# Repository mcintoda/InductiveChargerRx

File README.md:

# brim: bath level monitor

A sealed, Qi-charged sensor that suction-mounts in the bathtub. It sends a
notification to your iPhone (over Wi-Fi, no pairing) before the bath
overflows, and reports the water temperature.

- **Level:** a 6-pad capacitive ladder that senses through the enclosure wall (non-contact)
- **Temperature:** TMP117, ±0.1 °C
- **Radio:** ESP32-S3 Wi-Fi → free ntfy push notifications (iOS app)
- **Power:** 320 mAh protected LiPo (25.5 × 36 × 4.3 mm), BQ51050B Qi receiver/charger at 143 mA, ~6 months per charge (estimate). Charges lying flat on any Qi pad, like a phone
- **Build:** JLCPCB 4-layer PCB + SMT assembly, JLC3DP enclosure

> Also in this repo: **[`squeeze/`](squeeze/README.md)**, a pair of hand-held pebbles that pass squeezes back and forth (separate project, reuses brim's Qi charger block).

- [`docs/design.md`](docs/design.md): requirements, architecture, power budget, mechanics, firmware behaviour
- [`docs/placement-and-electrodes.md`](docs/placement-and-electrodes.md): board placement study and electrode design (with field simulation)
- [`docs/sensing-options.md`](docs/sensing-options.md): touch vs FDC1004 level sensing: board variants, compare mode, bench protocol, decision rules
- [`docs/sensing-infographic.html`](docs/sensing-infographic.html): interactive explainer of how the level and temperature sensing work electrically
- [`docs/branding.md`](docs/branding.md): name, mark, palette, and the debossed design features on the enclosure
- [`docs/pcb-routing.md`](docs/pcb-routing.md): routing pipeline and JLC order settings
- [`docs/bring-up.md`](docs/bring-up.md): bench test plan for the first boards
- [`firmware/`](firmware/): ESP-IDF firmware (ESP32-S3) with host unit tests
- **Product requirements (system, hardware, software):** [`docs/requirements.md`](docs/requirements.md)
- **Product website (marketing page):** [`docs/site/index.html`](docs/site/index.html)
- **Security review (Wi-Fi, web, OTA):** [`docs/security.md`](docs/security.md); firmware SBOM and CVE check: [`docs/sbom/`](docs/sbom/README.md)
- **Quick start guide for users:** [`docs/quick-start.html`](docs/quick-start.html) (setup, mounting, alerts, charging, light legend)
- [`docs/enclosure.md`](docs/enclosure.md): watertight enclosure (O-ring, no epoxy) with CAD in [`hardware/mech/`](hardware/mech/)
- **Parts JLC does not supply:** [`docs/bom-hand-parts.md`](docs/bom-hand-parts.md) (one BOM, all suppliers; CSV: [`hardware/bom_hand_parts.csv`](hardware/bom_hand_parts.csv))
- **Schematic without KiCad:** [`docs/schematic.pdf`](docs/schematic.pdf) (zoomable, searchable) or [`docs/img/schematic.svg`](docs/img/schematic.svg) / [`.png`](docs/img/schematic.png) (shows in the browser)
- [`hardware/kicad/`](hardware/kicad/): KiCad 7 project (schematic rev C, routed 4-layer PCB)
- [`hardware/bom_jlc.csv`](hardware/bom_jlc.csv): JLCPCB assembly BOM (generated; LCSC numbers still to be filled)
- [`hardware/tools/gen_schematic.py`](hardware/tools/gen_schematic.py): regenerates the schematic and BOM
- [`hardware/tools/gen_pcb.py`](hardware/tools/gen_pcb.py) / [`electrode_sim.py`](hardware/tools/electrode_sim.py): placement-study PCB and electrode simulation
- [`hardware/tools/verify_netlist.py`](hardware/tools/verify_netlist.py): checks that the drawn wiring matches the intended netlist

```
python3 hardware/tools/gen_schematic.py    # needs KiCad 7+ symbol libraries; also refreshes docs/schematic.pdf/.svg/.png
python3 hardware/tools/verify_netlist.py   # needs kicad-cli
```

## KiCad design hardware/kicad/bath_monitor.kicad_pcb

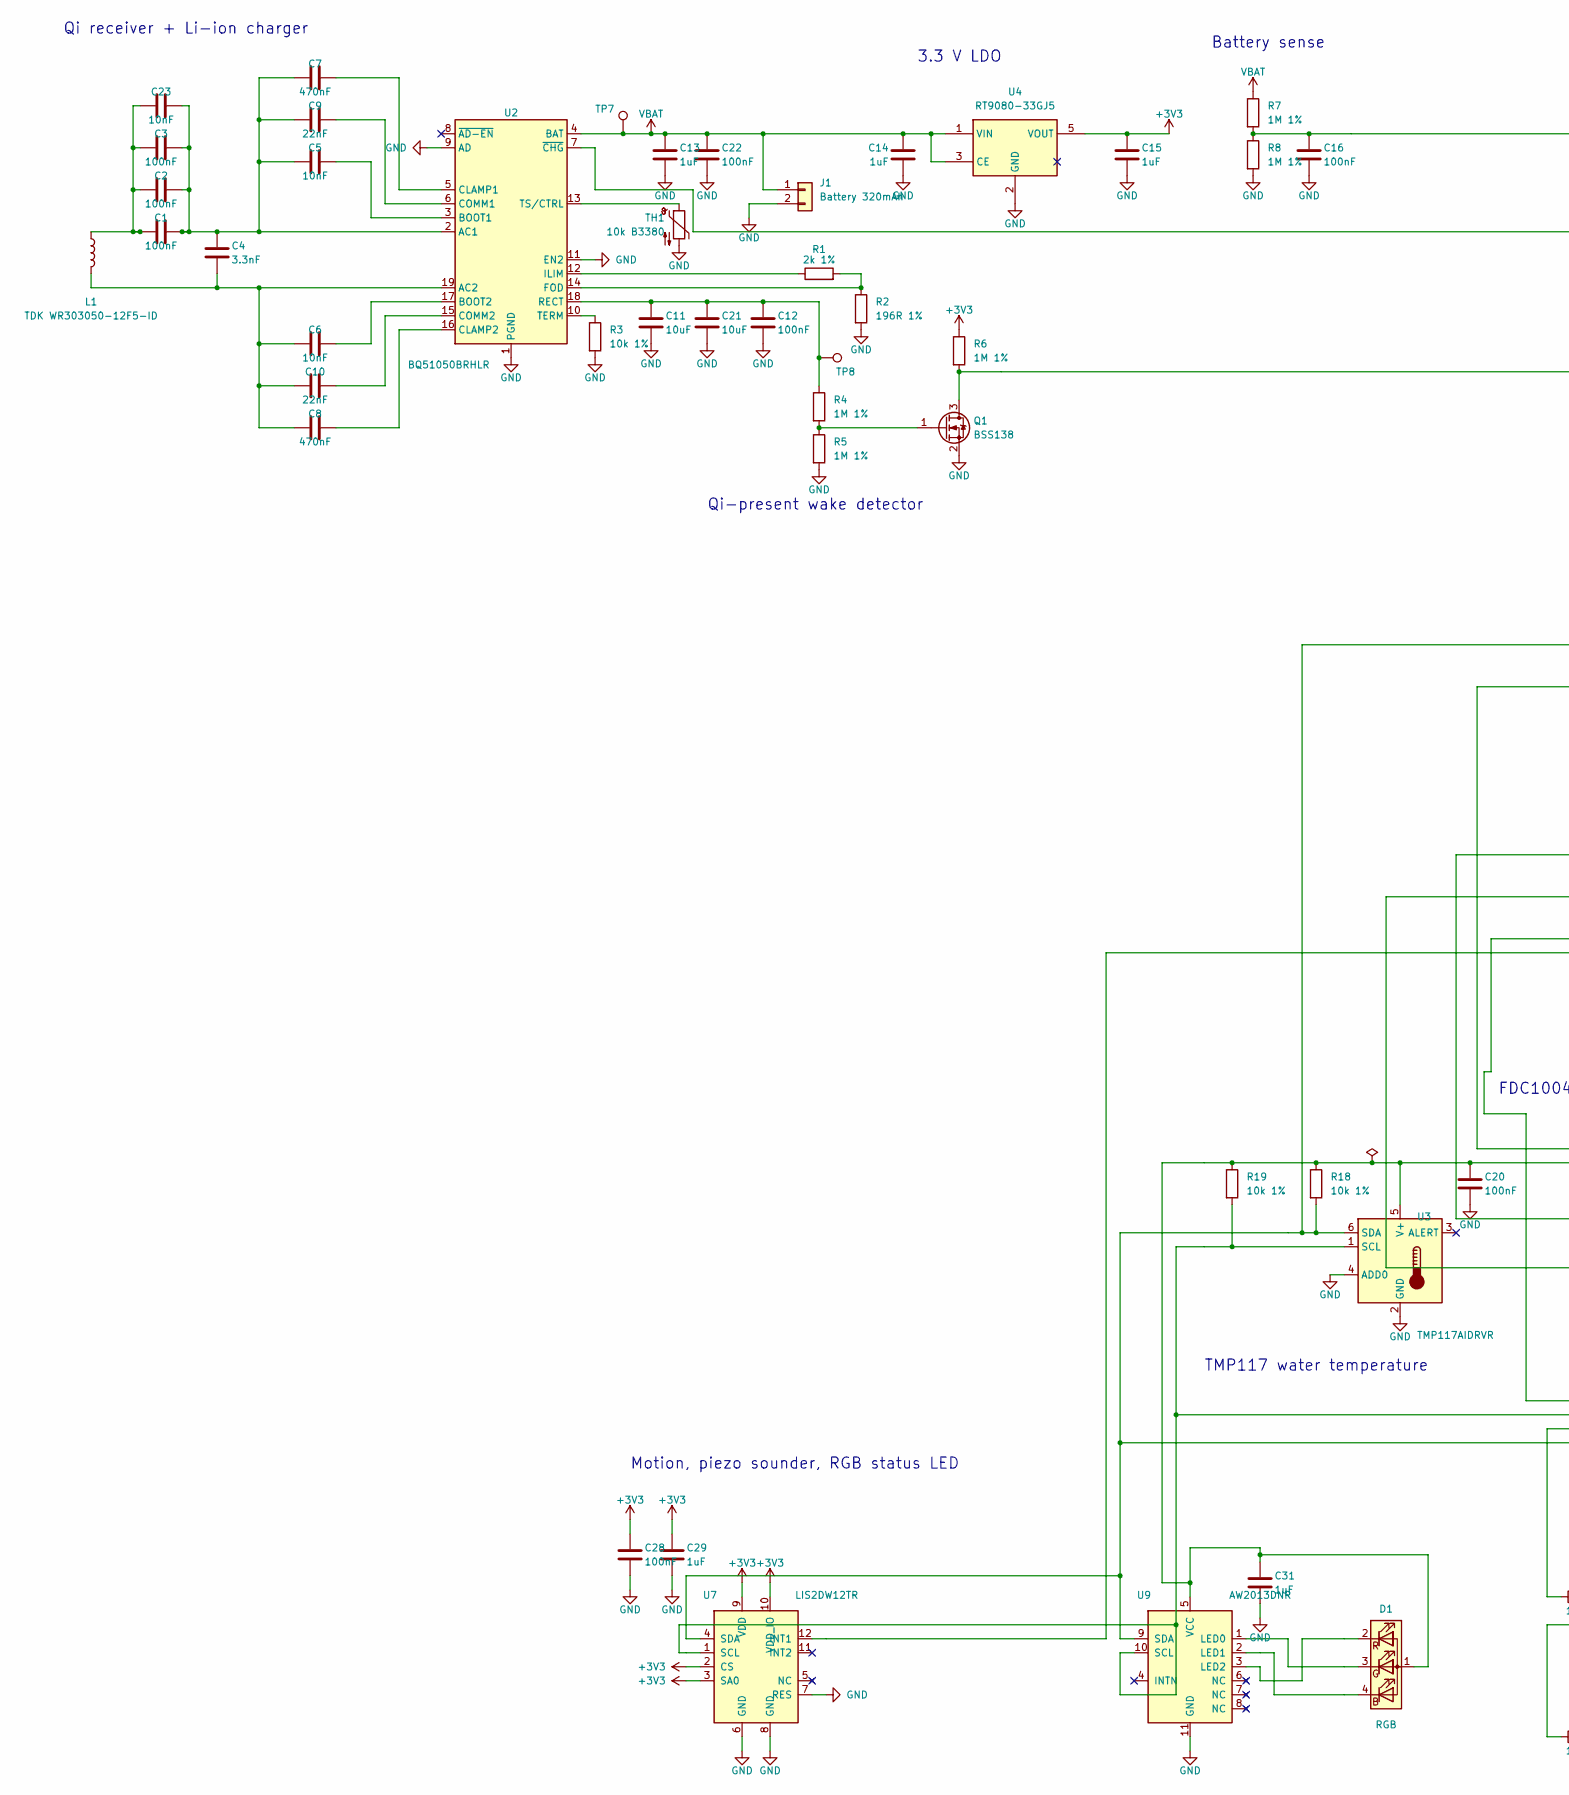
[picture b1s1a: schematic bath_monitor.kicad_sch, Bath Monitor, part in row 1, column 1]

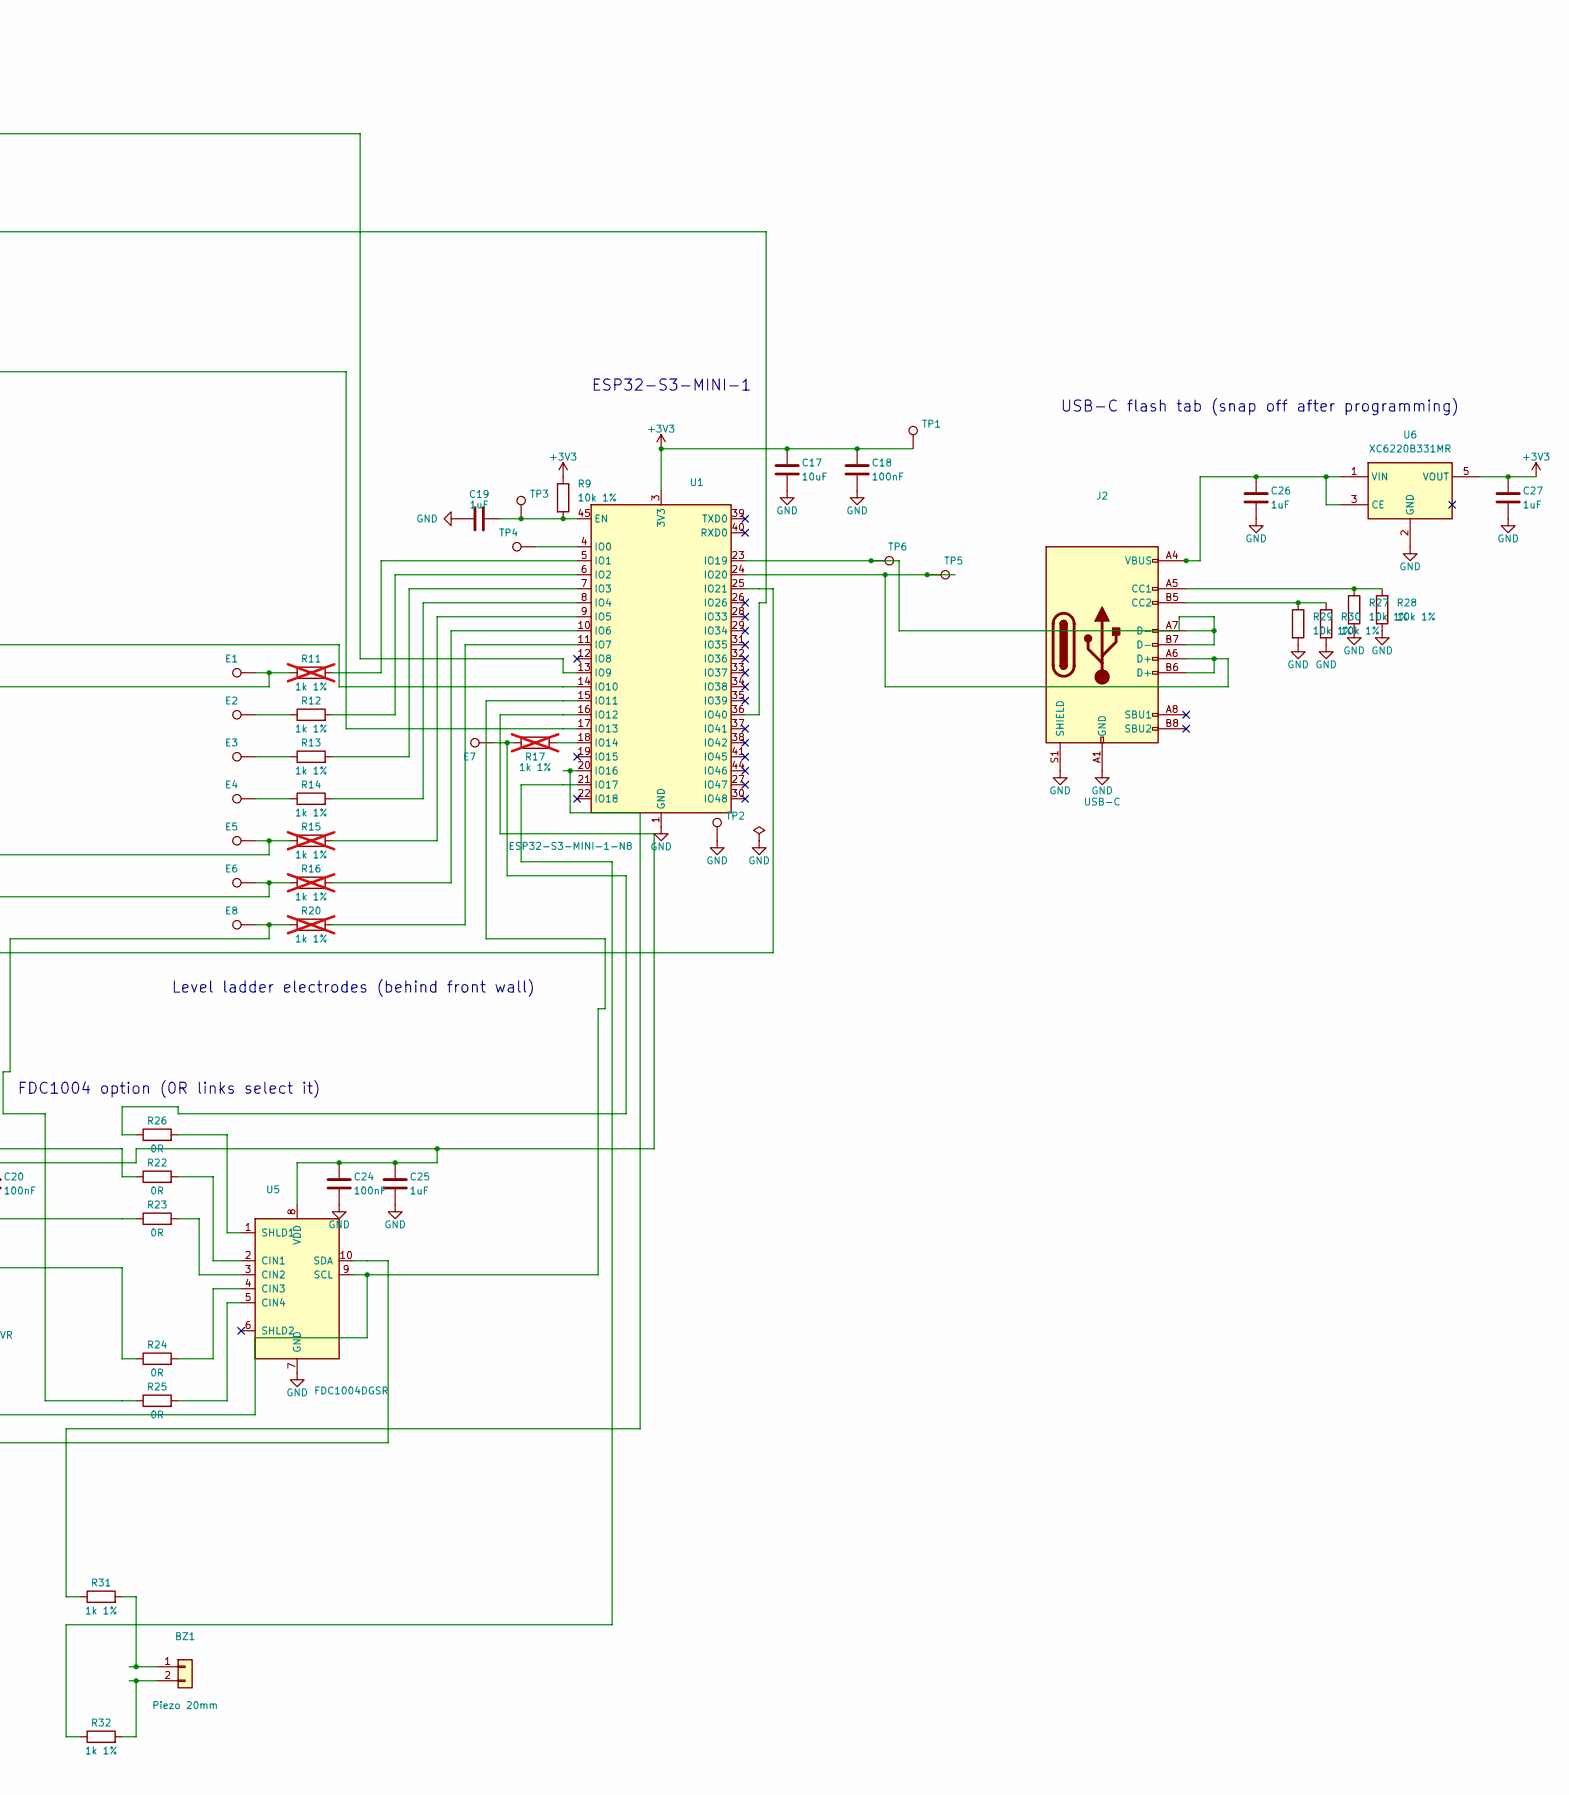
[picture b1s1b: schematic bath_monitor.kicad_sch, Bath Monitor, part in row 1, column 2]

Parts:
BZ1: Piezo 20mm; SolderWirePad_1x02_SMD_1x1.6mm_P2mm
C1, C2, C3, C12, C16, C18, C20, C22, C24, C28: 100nF; C_0603_1608Metric; Rating 50V X7R
C4: 3.3nF; C_0603_1608Metric; Rating 50V C0G
C5, C6, C23: 10nF; C_0402_1005Metric; Rating 50V X7R
C7, C8: 470nF; C_0603_1608Metric; Rating 25V X7R
C9, C10: 22nF; C_0402_1005Metric; Rating 50V X7R
C11, C17, C21: 10uF; C_0805_2012Metric; Rating 25V X5R
C13, C14, C15, C19, C25, C26, C27, C29, C31: 1uF; C_0402_1005Metric; Rating 25V X5R
D1: RGB; LED_RGB_1615_XINGLIGHT; MPN XL-1615RGBC-RF
E1: PAD1; TouchPad_30x9mm
E2: PAD2; TouchPad_30x9mm
E3: PAD3; TouchPad_30x9mm
E4: PAD4; TouchPad_30x9mm
E5: PAD5; TouchPad_30x9mm
E6: PAD6; TouchPad_30x9mm
E7: SHIELD; ShieldTap
E8: REF; RefPad_30x6mm
J1: Battery 320mAh; SolderWire-0.1sqmm_1x02_P3.6mm_D0.4mm_OD1mm
J2: USB-C; USB_C_Receptacle_HRO_TYPE-C-31-M-12; MPN TYPE-C-31-M-12
L1: TDK WR303050-12F5-ID; SolderWire-0.1sqmm_1x02_P3.6mm_D0.4mm_OD1mm; MPN TDK WR303050-12F5-ID; LCSC C6357742
Q1: BSS138; SOT-23
R1: 2k 1%; R_0402_1005Metric
R2: 196R 1%; R_0402_1005Metric
R3, R9, R18, R19, R27, R28, R29, R30: 10k 1%; R_0402_1005Metric
R4, R5, R6, R7, R8: 1M 1%; R_0402_1005Metric
R11, R15, R16, R17, R20: 1k 1%; R_0402_1005Metric; not fitted
R12, R13, R14, R31, R32: 1k 1%; R_0402_1005Metric
R22, R23, R24, R25, R26: 0R; R_0402_1005Metric
TH1: 10k B3380; R_0402_1005Metric; MPN Murata NCP15XH103F03RC
TP1: +3V3; TestPoint_Pad_D1.5mm
TP2: GND; TestPoint_Pad_D1.5mm
TP3: EN; TestPoint_Pad_D1.5mm
TP4: IO0; TestPoint_Pad_D1.5mm
TP5: USB_DP; TestPoint_Pad_D1.5mm
TP6: USB_DN; TestPoint_Pad_D1.5mm
TP7: VBAT; TestPoint_Pad_D1.5mm
TP8: RECT; TestPoint_Pad_D1.5mm
U1: ESP32-S3-MINI-1-N8; ESP32-S3-MINI-1; MPN ESP32-S3-MINI-1-N8
U2: BQ51050BRHLR; Texas_VQFN-RHL-20; MPN BQ51050BRHLR
U3: TMP117AIDRVR; WSON-6-1EP_2x2mm_P0.65mm_EP1x1.6mm; MPN TMP117AIDRVR
U4: RT9080-33GJ5; SOT-23-5
U5: FDC1004DGSR; VSSOP-10_3x3mm_P0.5mm; MPN FDC1004DGSR
U6: XC6220B331MR; SOT-23-5
U7: LIS2DW12TR; LGA-12_2x2mm_P0.5mm; MPN LIS2DW12TR
U9: AW2013DNR; DFN-10-1EP_2x2mm_P0.4mm_AW2013; MPN AW2013DNR

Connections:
+3V3: C15.1, C17.1, C18.1, C27.1, C28.1, C29.1, R6.1, R9.1, TP1.1, U1.3 (3V3), U4.5 (VOUT), U6.5 (VOUT), U7.2 (CS), U7.3 (SA0), U7.9 (VDD), U7.10 (VDD_IO)
AC1: C1.2, C2.2, C3.2, C4.1, C5.1, C7.1, C9.1, C23.2, U2.2 (AC1)
AC2: C4.2, C6.1, C8.1, C10.1, L1.2, U2.19 (AC2)
ACC_INT: U1.25 (IO21), U7.12 (INT1)
BOOT1: C5.2, U2.3 (BOOT1)
BOOT2: C6.2, U2.17 (BOOT2)
BUZ_A: R31.1, U1.20 (IO16)
BUZ_B: R32.1, U1.21 (IO17)
CHG_N: U1.36 (IO40), U2.7 (~CHG)
CLAMP1: C7.2, U2.5 (CLAMP1)
CLAMP2: C8.2, U2.16 (CLAMP2)
COIL_A: C1.1, C2.1, C3.1, C23.1, L1.1
COMM1: C9.2, U2.6 (COMM1)
COMM2: C10.2, U2.15 (COMM2)
EN: C19.2, R9.2, TP3.1, U1.45 (EN)
FDC_CIN1: R22.2, U5.2 (CIN1)
FDC_CIN2: R23.2, U5.3 (CIN2)
FDC_CIN3: R24.2, U5.4 (CIN3)
FDC_CIN4: R25.2, U5.5 (CIN4)
FDC_SHLD: R26.2, U5.1 (SHLD1)
FOD: R1.2, R2.1, U2.14 (FOD)
GND: C11.2, C12.2, C13.2, C14.2, C15.2, C16.2, C17.2, C18.2, C19.1, C20.2, C21.2, C22.2, C24.2, C25.2, C26.2, C27.2, C28.2, C29.2, C31.2, J1.2, J2.A1 (GND), J2.A12 (GND), J2.B1 (GND), J2.B12 (GND), J2.S1 (SHIELD), Q1.2 (S), R2.2, R3.2, R5.2, R8.2, R27.2, R28.2, R29.2, R30.2, TH1.2, TP2.1, U1.1 (GND), U1.2 (GND), U1.42 (GND), U1.43 (GND), U1.46 (GND), U1.47 (GND), U1.48 (GND), U1.49 (GND), U1.50 (GND), U1.51 (GND), U1.52 (GND), U1.53 (GND), U1.54 (GND), U1.55 (GND), U1.56 (GND), U1.57 (GND), U1.58 (GND), U1.59 (GND), U1.60 (GND), U1.61 (GND), U1.62 (GND), U1.63 (GND), U1.64 (GND), U1.65 (GND), U2.1 (PGND), U2.9 (AD), U2.11 (EN2), U2.20 (PGND), U2.21 (PGND), U3.2 (GND), U3.4 (ADD0), U3.7, U4.2 (GND), U5.7 (GND), U6.2 (GND), U7.6 (GND), U7.7 (RES), U7.8 (GND), U9.11 (GND)
ILIM: R1.1, U2.12 (ILIM)
IO0: TP4.1, U1.4 (IO0)
LED_B: D1.4 (BK), U9.2 (LED1)
LED_G: D1.3 (GK), U9.1 (LED0)
LED_R: D1.2 (RK), U9.3 (LED2)
NTC: TH1.1, U2.13 (TS/CTRL)
PAD1: E1.1, R11.1, R22.1
PAD2: E2.1, R12.1
PAD3: E3.1, R13.1
PAD4: E4.1, R14.1
PAD5: E5.1, R15.1, R23.1
PAD6: E6.1, R16.1, R24.1
PAD_REF: E8.1, R20.1, R25.1
PIEZO_A: BZ1.1, R31.2
PIEZO_B: BZ1.2, R32.2
QI_DET_N: Q1.3 (D), R6.2, U1.17 (IO13)
QI_GATE: Q1.1 (G), R4.2, R5.1
RECT: C11.1, C12.1, C21.1, R4.1, TP8.1, U2.18 (RECT)
SCL: R19.2, U1.15 (IO11), U3.1 (SCL), U5.9 (SCL), U7.1 (SCL), U9.10 (SCL)
SDA: R18.2, U1.14 (IO10), U3.6 (SDA), U5.10 (SDA), U7.4 (SDA), U9.9 (SDA)
SENSE_3V3: C20.1, C24.1, C25.1, C31.1, D1.1 (A), R18.1, R19.1, U1.16 (IO12), U3.5 (V+), U5.8 (VDD), U9.5 (VCC)
SHIELD: E7.1, R17.1, R26.1
SHIELD_DRV: R17.2, U1.18 (IO14)
TAB_CC1: J2.A5 (CC1), R27.1, R28.1
TAB_CC2: J2.B5 (CC2), R29.1, R30.1
TAB_VBUS: C26.1, J2.A4 (VBUS), J2.A9 (VBUS), J2.B4 (VBUS), J2.B9 (VBUS), U6.1 (VIN), U6.3 (CE)
TERM: R3.1, U2.10 (TERM)
TOUCH1: R11.2, U1.5 (IO1)
TOUCH2: R12.2, U1.6 (IO2)
TOUCH3: R13.2, U1.7 (IO3)
TOUCH4: R14.2, U1.8 (IO4)
TOUCH5: R15.2, U1.9 (IO5)
TOUCH6: R16.2, U1.10 (IO6)
TOUCH7: R20.2, U1.11 (IO7)
USB_DN: J2.A7 (D-), J2.B7 (D-), TP6.1, U1.23 (IO19)
USB_DP: J2.A6 (D+), J2.B6 (D+), TP5.1, U1.24 (IO20)
VBAT: C13.1, C14.1, C22.1, J1.1, R7.1, TP7.1, U2.4 (BAT), U4.1 (VIN), U4.3 (CE)
VBAT_SENSE: C16.1, R7.2, R8.1, U1.13 (IO9)

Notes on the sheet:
FDC1004 option (0R links select it)
USB-C flash tab (snap off after programming)
Qi receiver + Li-ion charger
Qi-present wake detector
3.3 V LDO
Battery sense
TMP117 water temperature
ESP32-S3-MINI-1
Level ladder electrodes (behind front wall)
Motion, piezo sounder, RGB status LED

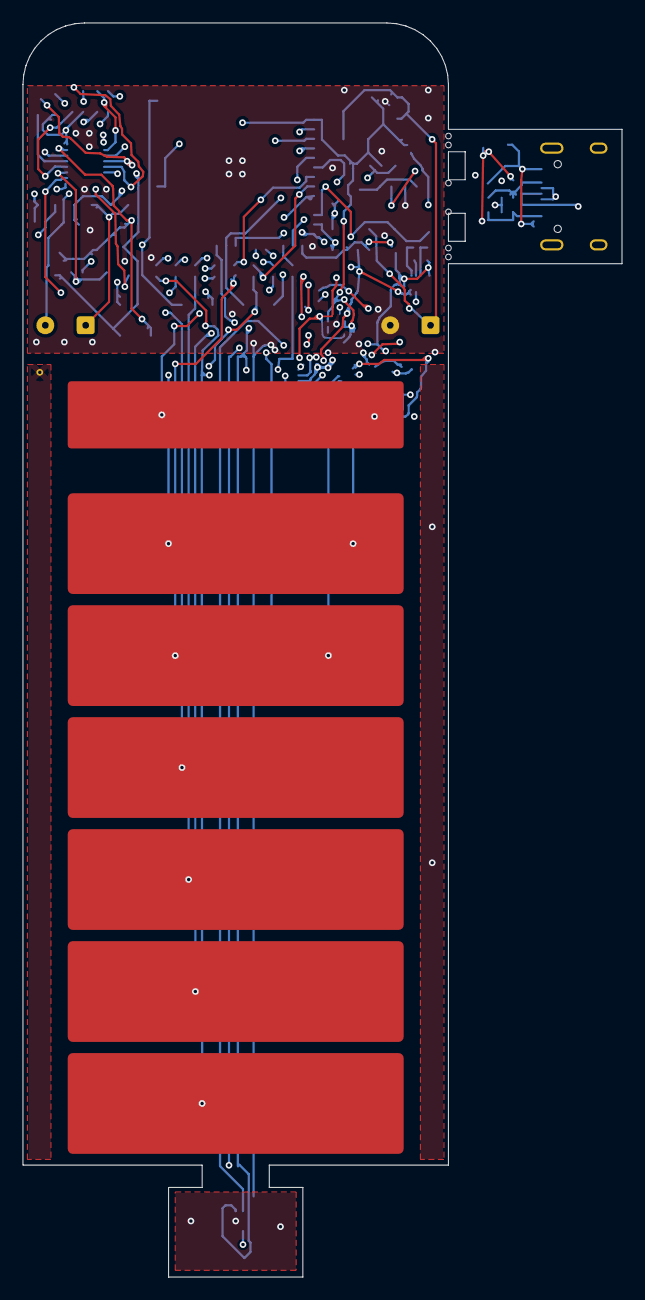
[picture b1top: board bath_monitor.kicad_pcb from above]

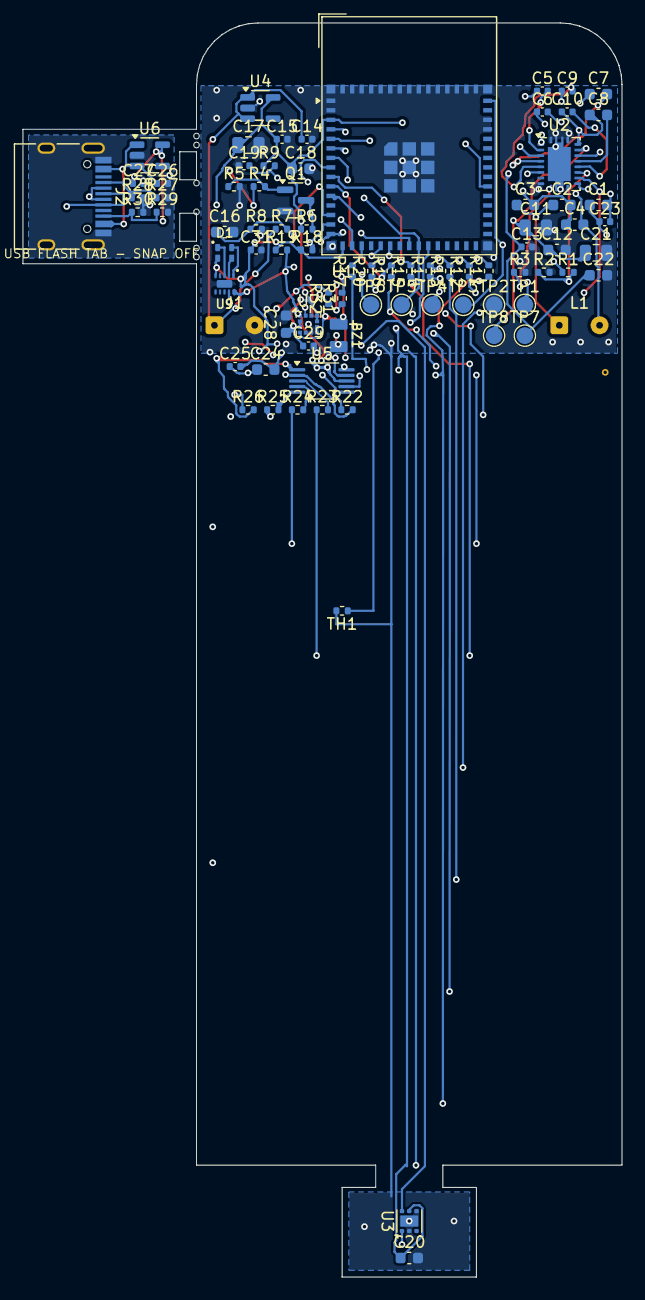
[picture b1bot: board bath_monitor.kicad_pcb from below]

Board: 4 copper layers, 53.5 x 112.0 mm, 91 parts (83 on the bottom side), 60 nets.

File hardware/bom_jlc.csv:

Comment,Designator,Footprint,LCSC Part #
Piezo 20mm,BZ1,SolderWirePad_1x02_SMD_1x1.6mm_P2mm,
100nF 50V X7R,"C1,C2,C3,C12,C16,C18,C20,C22,C24,C28",C_0603_1608Metric,
3.3nF 50V C0G,C4,C_0603_1608Metric,
10nF 50V X7R,"C5,C6,C23",C_0402_1005Metric,
470nF 25V X7R,"C7,C8",C_0603_1608Metric,
22nF 50V X7R,"C9,C10",C_0402_1005Metric,
10uF 25V X5R,"C11,C17,C21",C_0805_2012Metric,
1uF 25V X5R,"C13,C14,C15,C19,C25,C26,C27,C29,C31",C_0402_1005Metric,
RGB,D1,LED_RGB_1615_XINGLIGHT,
Battery 320mAh,J1,SolderWire-0.1sqmm_1x02_P3.6mm_D0.4mm_OD1mm,
USB-C,J2,USB_C_Receptacle_HRO_TYPE-C-31-M-12,
TDK WR303050-12F5-ID,L1,SolderWire-0.1sqmm_1x02_P3.6mm_D0.4mm_OD1mm,
BSS138,Q1,SOT-23,
2k 1%,R1,R_0402_1005Metric,
196R 1%,R2,R_0402_1005Metric,
10k 1%,"R3,R9,R18,R19,R27,R28,R29,R30",R_0402_1005Metric,
1M 1%,"R4,R5,R6,R7,R8",R_0402_1005Metric,
1k 1%,"R11,R12,R13,R14,R15,R16,R17,R20,R31,R32",R_0402_1005Metric,
0R,"R22,R23,R24,R25,R26",R_0402_1005Metric,
10k B3380,TH1,R_0402_1005Metric,
ESP32-S3-MINI-1-N8,U1,ESP32-S3-MINI-1,
BQ51050BRHLR,U2,Texas_VQFN-RHL-20,
TMP117AIDRVR,U3,WSON-6-1EP_2x2mm_P0.65mm_EP1x1.6mm,
RT9080-33GJ5,U4,SOT-23-5,
FDC1004DGSR,U5,VSSOP-10_3x3mm_P0.5mm,
XC6220B331MR,U6,SOT-23-5,
LIS2DW12TR,U7,LGA-12_2x2mm_P0.5mm,
AW2013DNR,U9,DFN-10-1EP_2x2mm_P0.4mm_AW2013,

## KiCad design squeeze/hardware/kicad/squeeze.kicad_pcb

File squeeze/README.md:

# squeeze: pass a squeeze across the house

Two soft, glowing pebbles, one for a parent and one for a child. Squeeze yours and the other one squeezes
its holder's hand with the same rhythm and strength, live. Squeeze a pattern; get it squeezed back.
It doesn't judge or score; it just passes squeezes back and forth.

- **Sense:** the whole pebble is a sealed air volume under a 2 mm silicone skin. A squeeze raises the pressure
  0.6–2+ kPa, read by a BMP280. Auto-ranging, so a child's squeeze counts as much as an adult's.
- **Squeeze back:** an SG90 servo turns an oval cam that pushes two curved plates 3 mm out into the palm and
  fingers, in proportion to the partner's squeeze.
- **Link:** ESP-NOW between the two units' ESP32-C3 modules: no router, no app, ~5 ms. Turn-taking: whoever squeezes first
  has the floor, and a squeeze back during the partner's still gets through (duplex sensing).
- **Power:** Qi charging (brim's BQ51050B block and coil), 400 mAh LiPo. Sleeps by itself and wakes on a squeeze or when the
  partner calls.
- **Enclosure:** 52 × 42 × 70 mm. Cast Dragon Skin 10 skin in each person's colour, glowing from inside. The 3D-printed
  mold is included.

| | |
|---|---|
| [`docs/design.md`](docs/design.md) | Requirements, sensing, mechanism, electronics, radio, behaviour and LED legend, enclosure and casting, build plan, safety, risks |
| [`docs/ordering.md`](docs/ordering.md) | **What to order where** (JLCPCB board + assembly, JLC3DP prints, hand parts), skin casting, assembly and first flash |
| [`docs/schematic.md`](docs/schematic.md) | The board's netlist, part by part (generated from `hardware/tools/parts.py`) |
| [`hardware/fab/`](hardware/fab/) | JLC order files: gerbers zip, `bom_jlc.csv`, `cpl_jlc.csv`, `hand_parts.csv` |
| [`firmware/`](firmware/) | ESP-IDF 5.3 (ESP32-C3). Pure logic host-tested: `make -C firmware/test` |
| [`hardware/mech/`](hardware/mech/) | CadQuery model, fit check and renders. STEP/STL in `out/` |
| [`docs/virtual-experiments.md`](docs/virtual-experiments.md) | Bring-up and usability rehearsed in simulation before ordering: two rounds, every problem found is fixed |
| [`firmware/sim/`](firmware/sim/) | Test bench: the real firmware for both units against simulated hardware and people |

```
# host tests and the two-unit simulation (no hardware)
make -C squeeze/firmware/test
(cd squeeze/firmware/sim && make && python3 experiments.py)
python3 squeeze/hardware/tools/erc.py              # static electrical checks

# firmware: one build per unit (same code, different role/colour/strength)
cd squeeze/firmware
. ~/esp/esp-idf/export.sh                          # ESP-IDF v5.3.2 (verified: both build, 0 warnings)
idf.py -B build-parent -D SDKCONFIG=build-parent/sdkconfig -D "SDKCONFIG_DEFAULTS=sdkconfig.defaults;sdkconfig.parent" set-target esp32c3 build
idf.py -B build-child  -D SDKCONFIG=build-child/sdkconfig  -D "SDKCONFIG_DEFAULTS=sdkconfig.defaults;sdkconfig.child"  set-target esp32c3 build
idf.py -B build-parent -p /dev/ttyACM0 flash monitor
# set the same "Pair secret" on both first: idf.py menuconfig -> Squeeze pair

# main board (KiCad 7: apt install kicad kicad-footprints kicad-symbols)
python3 squeeze/hardware/tools/gen_pcb.py         # board from parts.py: outline, placement, planes
python3 squeeze/hardware/tools/autoroute.py --jar freerouting-1.9.0.jar --passes 60   # Freerouting (Java 17+, xvfb-run)
python3 squeeze/hardware/tools/route.py           # finish: GND islands, last connections (brim's fixroute.py, adapted)
python3 squeeze/hardware/tools/hand_fixes_revA.py --gnd   # only if a GND pad is left on a pour island
python3 squeeze/hardware/tools/widen.py           # widen power tracks where the copper allows
python3 squeeze/hardware/tools/render_pcb.py      # docs/img/pcb_layers.png
python3 squeeze/hardware/tools/drc.py             # DRC summary
python3 squeeze/hardware/tools/jlc_outputs.py     # hardware/fab: gerbers zip, BOM, CPL, hand parts
python3 squeeze/hardware/tools/netlist_doc.py     # docs/schematic.md

# enclosure
python3 squeeze/hardware/mech/squeeze_unit.py     # STEP/STL
python3 squeeze/hardware/mech/fit_and_render.py   # interference check at rest and full swell, renders
```

Status: **rev A, ready to order.** Main board routed and DRC clean; JLC files in `hardware/fab/`; printed parts in
`hardware/mech/out/`; step by step in [docs/ordering.md](docs/ordering.md). Not yet built: the firmware builds with ESP-IDF
v5.3.2 and runs on the PC test bench, but has not run on the chip; the first boards need the bring-up checks in
design.md §9.

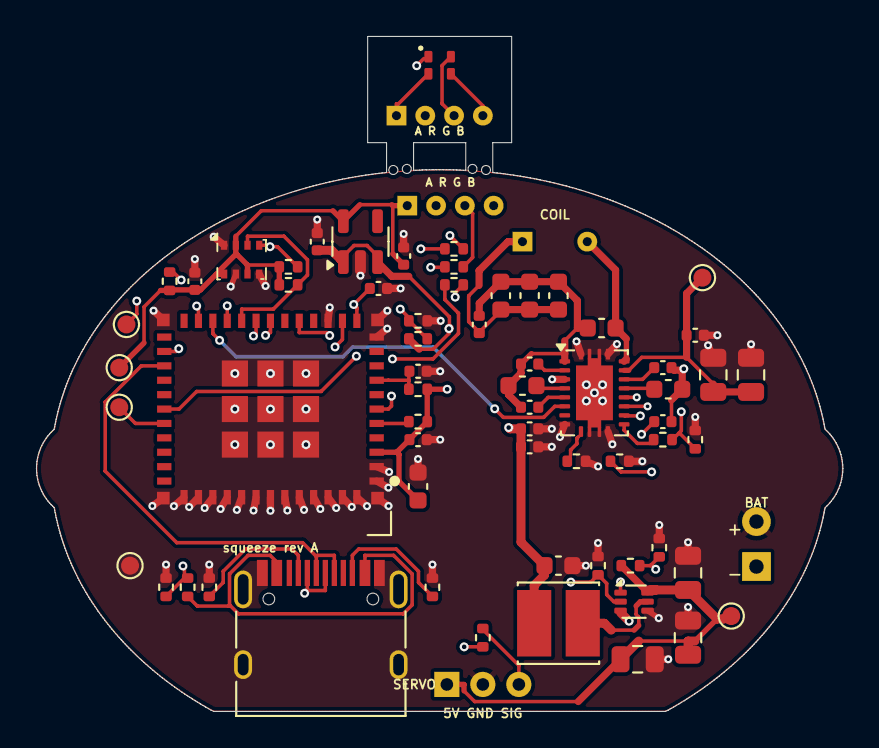
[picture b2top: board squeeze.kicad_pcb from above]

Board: 4 copper layers, 44.8 x 37.5 mm, 69 parts (0 on the bottom side), 47 nets.

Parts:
C1, C2, C3: 100nF; C_0603_1608Metric
C4: 3.3nF; C_0603_1608Metric
C5, C6, C23: 10nF; C_0402_1005Metric
C7, C8: 470nF; C_0603_1608Metric
C9, C10: 22nF; C_0402_1005Metric
C11, C21: 10uF; C_0805_2012Metric
C12, C22, C24, C25, C31: 100nF; C_0402_1005Metric
C13, C14, C15, C32: 1uF; C_0402_1005Metric
C16, C30: 10uF; C_0603_1608Metric
C17, C18, C19: 22uF; C_0805_2012Metric
D1: XL-1615RGBC-RF; LED_RGB_1615_XINGLIGHT
J1: Battery 503030; Wire_1x02_P2.5mm_D0.8mm
J2: Servo SG90; Wire_1x03_P2.0mm_D0.7mm
J3: TYPE-C-31-M-12; USB_C_Receptacle_HRO_TYPE-C-31-M-12
J4: LED wires; Wire_1x04_P1.6mm_D0.5mm
J5: LED tab wires; Wire_1x04_P1.6mm_D0.5mm
L1: TDK WR303050-12F5-ID; Wire_1x02_P3.6mm_D0.5mm
L2: 1uH; L_Cenker_CKCS4030
MB1: mouse bites
R1: 1.37k; R_0402_1005Metric
R2: 196; R_0402_1005Metric
R3, R30, R31, R32: 10k; R_0402_1005Metric
R4, R5: 1M; R_0402_1005Metric
R6, R7: 4.7k; R_0402_1005Metric
R8: 732k; R_0402_1005Metric
R9, R10, R15: 100k; R_0402_1005Metric
R11: 100; R_0402_1005Metric
R12, R13: 5.1k; R_0402_1005Metric
R14: 56k; R_0402_1005Metric
R16: 220; R_0402_1005Metric
R17, R18: 68; R_0402_1005Metric
TH1: 10k NTC B3380; R_0402_1005Metric
TP1: BOOT; TestPoint_Pad_D1.0mm
TP2: TXD; TestPoint_Pad_D1.0mm
TP3: GND; TestPoint_Pad_D1.0mm
TP5: +3V3; TestPoint_Pad_D1.0mm
TP6: +5V; TestPoint_Pad_D1.0mm
TP7: RECT; TestPoint_Pad_D1.0mm
U1: ESP32-C3-MINI-1U-N4; ESP32-C3-MINI-1U
U2: BQ51050BRHLR; Texas_VQFN-RHL-20
U3: RT9080-33GJ5; TSOT-23-5
U4: BMP280; Bosch_LGA-8_2x2.5mm_P0.65mm_ClockwisePinNumbering
U5: TPS61023DRLR; SOT-563

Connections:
+3V3: C15.1, C25.1, C30.1, C31.1, J4.1, R6.1, R7.1, R30.1, R31.1, R32.1, TP5.1, U1.3, U3.5, U4.2, U4.6, U4.8
+5V: C17.1, C18.1, C19.1, J2.1, R8.1, TP6.1, U5.6
AC1: C1.2, C2.2, C3.2, C4.1, C5.1, C7.1, C9.1, C23.2, U2.2
AC2: C4.2, C6.1, C8.1, C10.1, L1.2, U2.19
BOOT: TP1.1, U1.23
BOOT1: C5.2, U2.3
BOOT2: C6.2, U2.17
CC1: J3.A5, R12.1
CC2: J3.B5, R13.1
CHG_N: R32.2, U1.22, U2.7
CLAMP1: C7.2, U2.5
CLAMP2: C8.2, U2.16
COIL_A: C1.1, C2.1, C3.1, C23.1, L1.1
COMM1: C9.2, U2.6
COMM2: C10.2, U2.15
EN: C32.1, R30.2, U1.8
FB: R8.2, R9.1, U5.1
FOD: R1.2, R2.1, U2.14
GND: C11.2, C12.2, C13.2, C14.2, C15.2, C16.2, C17.2, C18.2, C19.2, C21.2, C22.2, C24.2, C25.2, C30.2, C31.2, C32.2, J1.2, J2.2, J3.A1, J3.A12, J3.B1, J3.B12, J3.S1, R2.2, R3.2, R5.2, R9.2, R10.2, R12.2, R13.2, R15.2, TH1.2, TP3.1, U1.1, U1.2, U1.11, U1.14, U1.36, U1.37, U1.38, U1.39, U1.40, U1.41, U1.42, U1.43, U1.44, U1.45, U1.46, U1.47, U1.48, U1.49, U1.50, U1.51, U1.52, U1.53, U2.1, U2.9, U2.11, U2.20, U2.21, U3.2, U4.1, U4.5, U4.7, U5.4
ILIM: R1.1, U2.12
IO2: R31.2, U1.5
LED_B: R18.1, U1.19
LED_BK: J4.4, R18.2
LED_G: R17.1, U1.18
LED_GK: J4.3, R17.2
LED_R: R16.1, U1.6
LED_RK: J4.2, R16.2
NTC: TH1.1, U2.13
RECT: C11.1, C12.1, C21.1, TP7.1, U2.18
SCL: R7.2, U1.21, U4.4
SDA: R6.2, U1.20, U4.3
SERVO_EN: R10.1, U1.30, U5.2
SERVO_PWM: R11.1, U1.16
SERVO_SIG: J2.3, R11.2
SW: L2.2, U5.5
TAB_A: D1.1, J5.1
TAB_B: D1.4, J5.4
TAB_G: D1.3, J5.3
TAB_R: D1.2, J5.2
TERM: R3.1, U2.10
TXD: TP2.1, U1.31
USB_DN: J3.A7, J3.B7, U1.26
USB_DP: J3.A6, J3.B6, U1.27
VBAT: C13.1, C14.1, C16.1, C22.1, J1.1, L2.1, R4.1, U2.4, U3.1, U3.3, U5.3
VBAT_SENSE: C24.1, R4.2, R5.1, U1.12
VBUS: J3.A4, J3.A9, J3.B4, J3.B9, R14.1
VBUS_SENSE: R14.2, R15.1, U1.13

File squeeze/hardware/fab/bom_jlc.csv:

Comment,Designator,Footprint,LCSC Part #
100nF 50V X7R 0603,"C1,C2,C3",C_0603_1608Metric,
3.3nF 50V C0G 0603,C4,C_0603_1608Metric,
10nF 50V X7R 0402,"C5,C6,C23",C_0402_1005Metric,
470nF 25V X7R 0603,"C7,C8",C_0603_1608Metric,
22nF 50V X7R 0402,"C9,C10",C_0402_1005Metric,
10uF 25V X5R 0805,"C11,C21",C_0805_2012Metric,
100nF 50V X7R 0402,C12,C_0402_1005Metric,
1uF 10V X5R 0402,"C13,C14,C15,C32",C_0402_1005Metric,
10uF 10V X5R 0603,"C16,C30",C_0603_1608Metric,
22uF 10V X5R 0805,"C17,C18,C19",C_0805_2012Metric,
100nF 16V X7R 0402,"C22,C24,C25,C31",C_0402_1005Metric,
XL-1615RGBC-RF,D1,LED_RGB_1615_XINGLIGHT,C965840
TYPE-C-31-M-12,J3,USB_C_Receptacle_HRO_TYPE-C-31-M-12,C165948
1uH 4030 shielded,L2,L_Cenker_CKCS4030,C5291823
1.37k 1% 0402,R1,R_0402_1005Metric,
196 1% 0402,R2,R_0402_1005Metric,
10k 1% 0402,"R3,R30,R31,R32",R_0402_1005Metric,
1M 1% 0402,"R4,R5",R_0402_1005Metric,
4.7k 1% 0402,"R6,R7",R_0402_1005Metric,
732k 1% 0402,R8,R_0402_1005Metric,
100k 1% 0402,"R9,R10,R15",R_0402_1005Metric,
100 1% 0402,R11,R_0402_1005Metric,
5.1k 1% 0402,"R12,R13",R_0402_1005Metric,
56k 1% 0402,R14,R_0402_1005Metric,
220 1% 0402,R16,R_0402_1005Metric,
68 1% 0402,"R17,R18",R_0402_1005Metric,
10k NTC B3380,TH1,R_0402_1005Metric,C77131
ESP32-C3-MINI-1U-N4,U1,ESP32-C3-MINI-1U,C2911374
BQ51050BRHLR,U2,Texas_VQFN-RHL-20,C133307
RT9080-33GJ5,U3,TSOT-23-5,C841192
BMP280,U4,Bosch_LGA-8_2x2.5mm_P0.65mm_ClockwisePinNumbering,C83291
TPS61023DRLR,U5,SOT-563,C919459

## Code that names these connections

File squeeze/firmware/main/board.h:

/* squeeze main board rev A: ESP32-C3-MINI-1U (hardware/tools/parts.py is the source of truth).
 * Strapping pins: GPIO2 pulled up (unused), GPIO8 pulled up (also the charger's open-drain CHG),
 * GPIO9 = BOOT test pad (internal pull-up). */
#pragma once

#define PIN_VBAT_ADC    0   /* battery / 2 (1M/1M + 100 nF), ADC1_CH0 */
#define ADC_CH_VBAT     ADC_CHANNEL_0
#define PIN_VBUS_SENSE  1   /* USB plugged in: 5 V x 100k/156k = 3.2 V */
#define PIN_LED_R       3   /* RGB LED cathodes via 220 / 68 / 68 ohm; common anode on 3V3: active low */
#define PIN_LED_G       4
#define PIN_LED_B       5
#define PIN_SDA         6   /* BMP280 */
#define PIN_SCL         7
#define PIN_CHG_N       8   /* BQ51050B CHG, low while charging */
#define PIN_SERVO_PWM   10  /* 100 ohm to the servo signal wire */
#define PIN_SERVO_EN    20  /* TPS61023 EN (100k pull-down): 5 V on, fully disconnected when low */

#define LED_ACTIVE_LOW  1
#define BMP280_ADDR     0x76 /* SDO to GND */

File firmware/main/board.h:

// brim bath monitor - pin map (schematic rev B, hardware/kicad/bath_monitor.kicad_sch)
#pragma once
#include "driver/gpio.h"
#include "driver/touch_pad.h"

#define N_LEVEL_PADS 6
#define N_SENSE_PADS 7                    // 6 level pads + dry reference pad
// touch channels: index 0..5 = PAD1 (bottom, wake) .. PAD6 (top), index 6 = REF
static const touch_pad_t SENSE_CH[N_SENSE_PADS] = {
    TOUCH_PAD_NUM1, TOUCH_PAD_NUM2, TOUCH_PAD_NUM3, TOUCH_PAD_NUM4, TOUCH_PAD_NUM5, TOUCH_PAD_NUM6, TOUCH_PAD_NUM7};
// deep-sleep wake pad: PAD1, or PAD2 when the FDC1004 links are fitted (its ESD diodes clamp PAD1 with the rail off)
#define GUARD_CH         TOUCH_PAD_NUM8   // unconnected (IO8); the shield, not a guard ring, does the work
// shield = TOUCH_PAD_NUM14 (GPIO14), selected automatically by the waterproof function

#define PIN_VBAT_SENSE   GPIO_NUM_9       // ADC1_CH8, 1M/1M divider
#define PIN_SDA          GPIO_NUM_10
#define PIN_SCL          GPIO_NUM_11
#define PIN_SENSE_PWR    GPIO_NUM_12      // powers TMP117, FDC1004, AW2013 + RGB LED, I2C pull-ups
#define PIN_QI_DET_N     GPIO_NUM_13      // low while on a Qi pad (RTC GPIO, ext1 wake)
#define PIN_CHG_N        GPIO_NUM_40      // BQ51050B CHG, open drain, low while charging
#define PIN_ACC_INT      GPIO_NUM_21      // LIS2DW12 INT1, active low push-pull (RTC GPIO, ext1 wake)
#define PIN_BUZ_A        GPIO_NUM_16      // piezo disc, driven in antiphase with BUZ_B through 1k each
#define PIN_BUZ_B        GPIO_NUM_17

#define TMP117_ADDR      0x48
#define LIS2DW12_ADDR    0x19             // SA0 tied high (no pull-up current)
#define AW2013_ADDR      0x45
